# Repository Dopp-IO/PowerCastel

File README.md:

# PowerCastel
Tiny castellated adaptation of Adafruit PowerBoost 1000C.

Part	Value	        Package  
C1	  10uF	        C0603  
C2  	2.2uF	        C0603  
C4	  0.1uF       	C0603  
C6  	100uF	        C0805  
C7  	10uF	        C0603  
L1  	6.8uH	        INDUCTOR_5X5MM_TDK_VLC5045  
R1  	1.87M	        R0603  
R2  	340K	        R0603  
R3  	1.87M	        R0603  
R4  	200K	        R0603  
R6  	270K	        R0603  
R7  	100K	        R0603  
R13 	200K	        R0603  
R16 	1.0K	        R0603  
R17 	100K	        R0603  
THERM	15K	          R0603  
T1    MMUN2114      SC59-BEC  
U1	  TPS61090RSAR	PVQFN-16  
U2	  MCP73871	    QFN20_4MM

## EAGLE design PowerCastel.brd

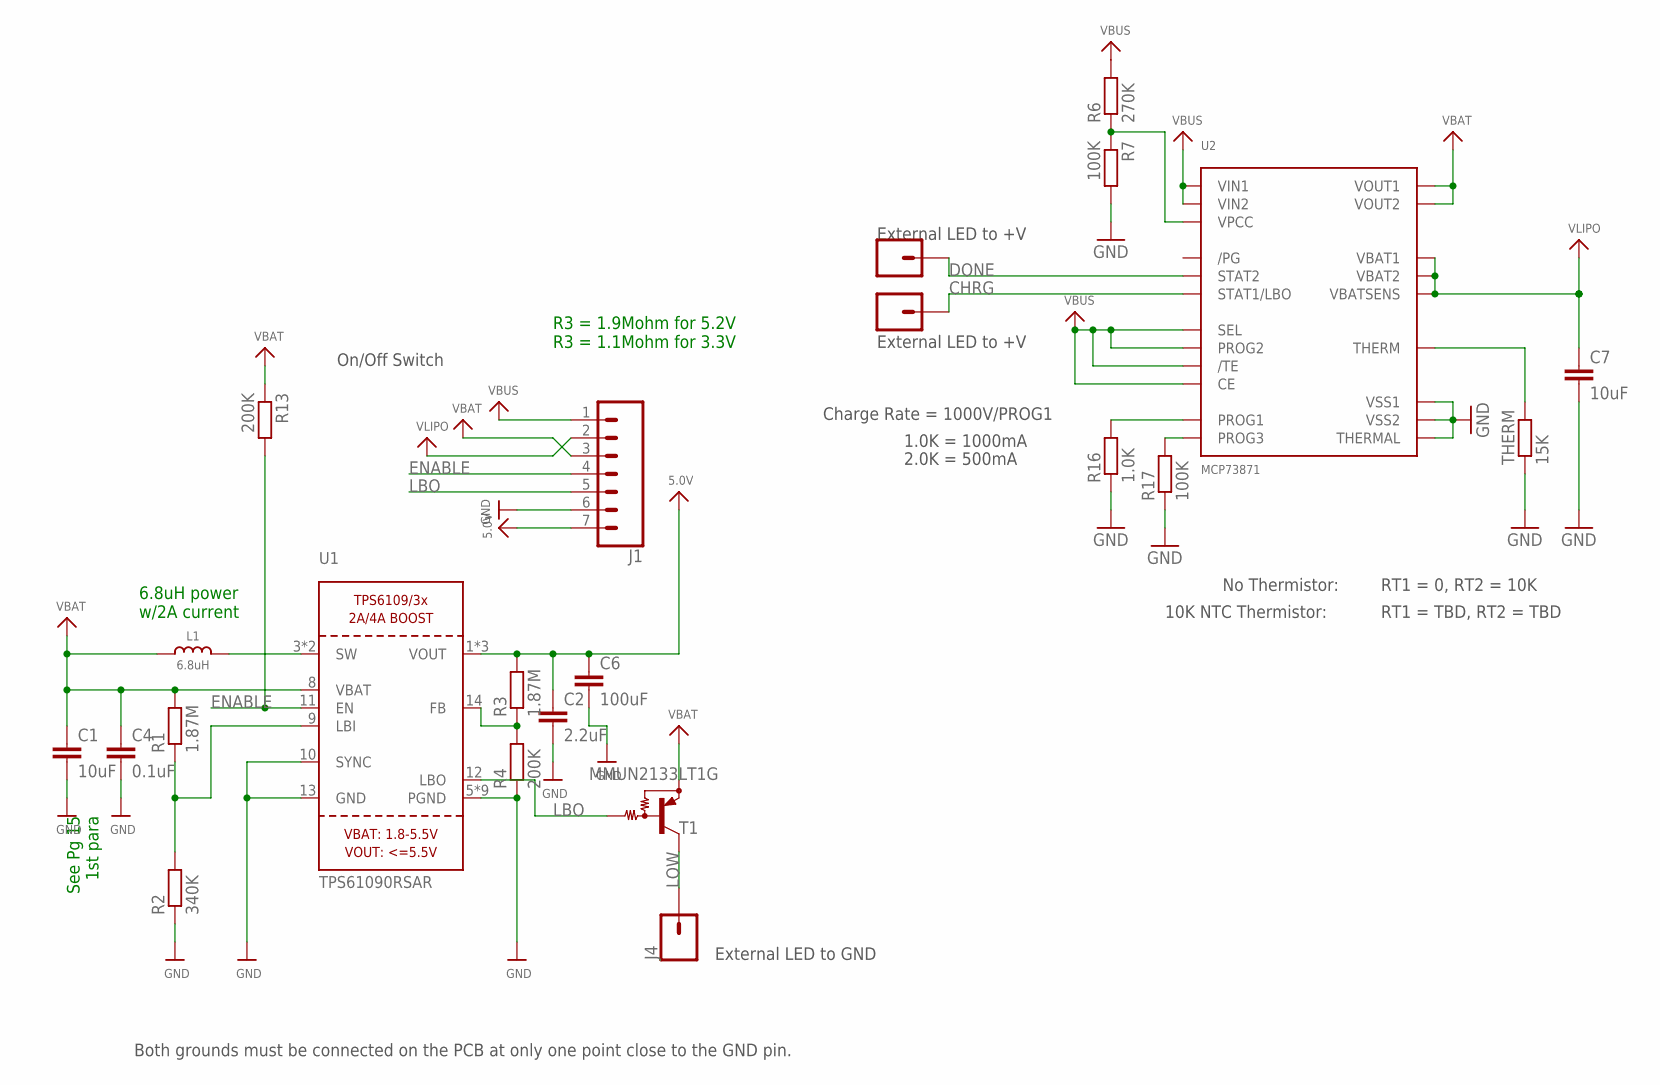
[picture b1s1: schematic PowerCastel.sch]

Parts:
C1, C7: 10uF; C0603
C2: 2.2uF; C0603
C4: 0.1uF; C0603
C6: 100uF; C0805
J1: CONN_07NO_SILK; 1X07_NO_SILK
J2, J3, J4: CONN_01PTH_NO_SILK_YES_STOP; 1X01_NO_SILK
L1: 6.8uH; INDUCTOR_5X5MM_TDK_VLC5045
R1, R3: 1.87M; R0603
R2: 340K; R0603
R4, R13: 200K; R0603
R6: 270K; R0603
R7, R17: 100K; R0603
R16: 1.0K; R0603
T1: MMUN2133LT1G; SC59-BEC
THERM: 15K; R0603
U1: TPS61090RSAR; PVQFN-16
U2: MCP73871; QFN20_4MM

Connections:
5.0V: C2.1, C6.1, J1.7, R3.2, U1.1 (VOUT), U1.15 (VOUT), U1.16 (VOUT)
CHRG: J3.1, U2.P$8 (STAT1/LBO)
DONE: J2.1, U2.P$7 (STAT2)
ENABLE: J1.4, R13.2, U1.11 (EN)
GND: C1.2, C2.2, C4.2, C6.2, C7.2, J1.6, R2.1, R4.1, R7.2, R16.1, R17.1, THERM.1, U1.5 (PGND), U1.6 (PGND), U1.7 (PGND), U1.10 (SYNC), U1.13 (GND), U1.P$18 (PGND), U1.P$19 (PGND), U1.P$20 (PGND), U1.P$21 (PGND), U1.P$22 (PGND), U1.THERMAL (PGND), U2.P$10 (VSS1), U2.P$11 (VSS2), U2.P$21 (THERMAL)
LBO: J1.5, T1.B, U1.12 (LBO)
LOW: J4.1, T1.C
unnamed: L1.P$2 (2), U1.3 (SW), U1.4 (SW)
unnamed: R1.1, R2.2, U1.9 (LBI)
unnamed: R3.1, R4.2, U1.14 (FB)
unnamed: R6.1, R7.1, U2.P$2 (VPCC)
unnamed: THERM.2, U2.P$5 (THERM)
unnamed: R17.2, U2.P$12 (PROG3)
unnamed: R16.2, U2.P$13 (PROG1)
VBAT: C1.1, C4.1, J1.3, L1.P$1 (1), R1.2, R13.1, T1.E, U1.8 (VBAT), U2.P$1 (VOUT1), U2.P$20 (VOUT2)
VBUS: J1.1, R6.2, U2.P$3 (SEL), U2.P$4 (PROG2), U2.P$9 (/TE), U2.P$17 (CE), U2.P$18 (VIN1), U2.P$19 (VIN2)
VLIPO: C7.1, J1.2, U2.P$14 (VBAT1), U2.P$15 (VBAT2), U2.P$16 (VBATSENS)

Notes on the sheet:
Both grounds must be connected on the PCB at only one point close to the GND pin.
On/Off Switch
See Pg 15 1st para
6.8uH power w/2A current
R3 = 1.9Mohm for 5.2V R3 = 1.1Mohm for 3.3V
Charge Rate = 1000V/PROG1
1.0K = 1000mA
2.0K = 500mA
No Thermistor:
10K NTC Thermistor:
RT1 = 0, RT2 = 10K
RT1 = TBD, RT2 = TBD
External LED to GND
External LED to +V

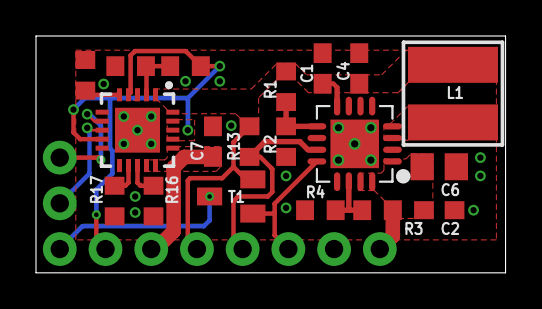
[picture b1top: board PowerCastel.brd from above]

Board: 2 copper layers, 26.1 x 13.2 mm, 23 parts (0 on the bottom side), 17 nets.

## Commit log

2018-08-11 Added eagles, gerbers and pdf
2018-08-11 Added BOM
2018-08-12 Fixed ground planes and added power planes
    Ground plane connection to components on left side of board has been widened. Added power planes as specified by TPS61090 datasheet.
2018-08-12 Fixed ground via
2019-01-20 Updated design
    New design has improved ground plane and has better support for external LEDs.
2019-01-20 Updated schematic
    Includes PNP LED driver
2019-01-20 Added T1 and updated packages

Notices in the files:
parts and their libraries:
SparkFun-Connectors: Licensing: Creative Commons ShareAlike 4.0 International - https://creativecommons.org/licenses/by-sa/4.0
microbuilder: This work is placed in the public domain, and may be freely used for commercial and non-commercial work with the following conditions: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
